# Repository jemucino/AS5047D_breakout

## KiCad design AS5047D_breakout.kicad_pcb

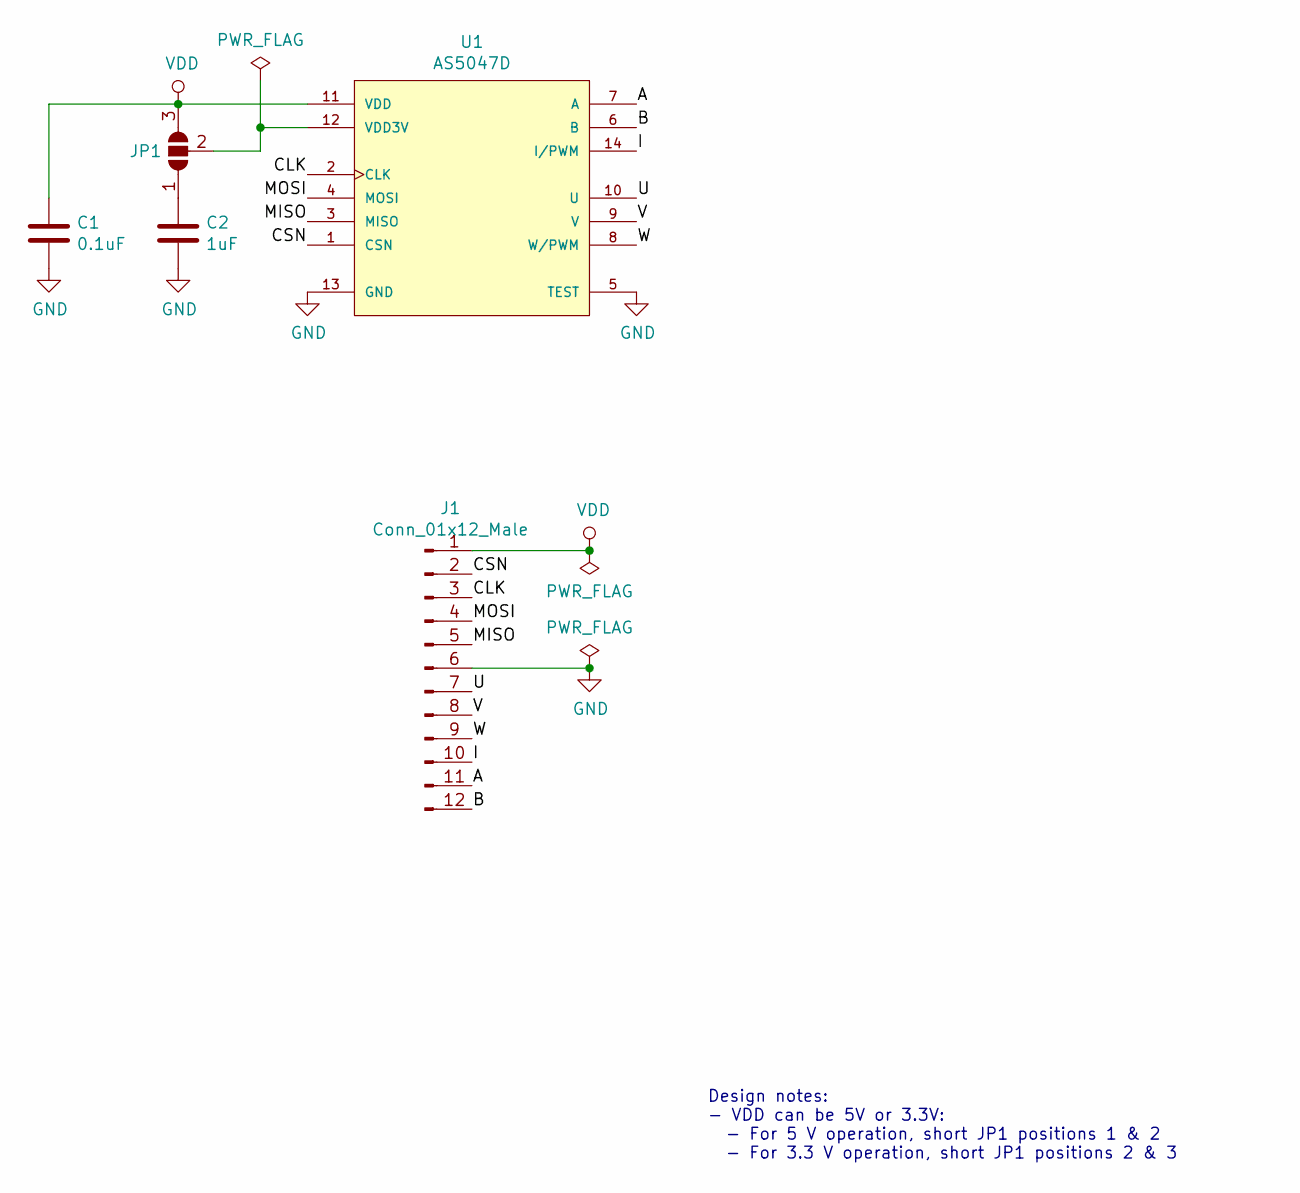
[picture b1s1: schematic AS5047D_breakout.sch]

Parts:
C1: 0.1uF; C_0603_1608Metric
C2: 1uF; C_0603_1608Metric
J1: Conn_01x12_Male; Amphenol_SFV12R
JP1: SolderJumper_3_Open; SolderJumper-3_P1.3mm_Open_RoundedPad1.0x1.5mm_NumberLabels
U1: AS5047D; TSSOP-14_4.4x5mm_P0.65mm

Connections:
/A: J1.11, U1.7 (A)
/B: J1.12, U1.6 (B)
/CLK: J1.3, U1.2 (CLK)
/CSN: J1.2, U1.1 (CSN)
/I: J1.10, U1.14 (I/PWM)
/MISO: J1.5, U1.3 (MISO)
/MOSI: J1.4, U1.4 (MOSI)
/U: J1.7, U1.10 (U)
/V: J1.8, U1.9 (V)
/W: J1.9, U1.8 (W/PWM)
GND: C1.2, C2.2, J1.6, U1.5 (TEST), U1.13 (GND)
unnamed: C2.1, JP1.1 (A)
unnamed: JP1.2 (C), U1.12 (VDD3V)
VDD: C1.1, J1.1, JP1.3 (B), U1.11 (VDD)

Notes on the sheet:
Design notes: - VDD can be 5V or 3.3V: - For 5 V operation, short JP1 positions 1 & 2 - For 3.3 V operation, short JP1 positions 2 & 3

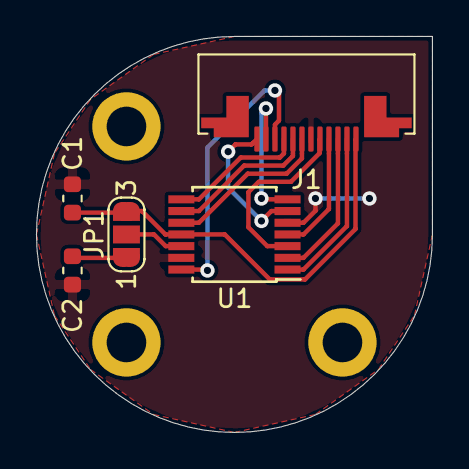
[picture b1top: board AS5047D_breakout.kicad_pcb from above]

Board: 2 copper layers, 22.0 x 22.0 mm, 5 parts (0 on the bottom side), 14 nets.

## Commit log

2019-04-25 Transfer design from Eagle to KiCad
2019-04-25 Run PCBNew to cache footprints
2019-04-25 Create encoder breakout board layout
2019-04-26 Adjust harness connector location on AS5047D board
2019-04-26 Modify AS5047D breakout form factor
2019-04-26 Remove fp-info-cache from version control
